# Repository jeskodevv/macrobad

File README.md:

# macropad but its evil >:]

hackclub stardance macropad mission, but its evil. it has shortcuts for things i do frequently, and hyperfocus mode. 

for details about the design process or other information, check out the [stardance devlogs](https://stardance.hackclub.com/projects/25784). A local copy is available in [JOURNAL.md](https://github.com/jeskodevv/macrobad/blob/main/JOURNAL.md).

## WHAT IT HAS

- SEEEDUINO RP2040 MCU
- 5x SWITCHES
- 1X ROTARY KNOB
- 0.91' OLED SCREEN
- RGB LED
- awesome design inspired by original hackpad itself :D

## WHAT IT CAN (FEATURES WIP)

- nothing xD (for now)

## HARDWARE OVERVIEW

**MacroBad :D** is 2-layer Printed Circuit Board and it has **seeeduino rp2040** as its core

here's the schematic

and here's the board design

### BOM

Bill of Materials also available in [BOM.csv](https://github.com/jeskodevv/macrobad/blob/main/BOM.csv) too.

## SOFTWARE OVERVIEW

imagine here's smth meaningful

## LINKS

- [Wiki [WIP]](https://github.com/jeskodevv/motrix/wiki)
- [Development Journal](https://stasis.hackclub.com/dashboard/discover/cmnlk2lji00hk01qlbceh9il3)
- [PCB Gerber Files](https://github.com/jeskodevv/motrix/blob/main/src/PCB/)
- [Arduino Library](https://github.com/jeskodevv/motrix/releases/tag/library)
- [Example Sketches [WIP]](https://github.com/jeskodevv/motrix/tree/main/src/examples)
- [BOM](https://github.com/jeskodevv/motrix/blob/main/BOM.csv)

## LICENSE

the whole project is licensed under **MIT**, meaning you can do whatever with this project.

See [LICENSE](https://github.com/jeskodevv/motrix/blob/main/LICENSE) for full terms.

---

Made with ❤ and [Hack](https://hackclub.com) by [@jeskodevv](https://github.com/jeskodevv)

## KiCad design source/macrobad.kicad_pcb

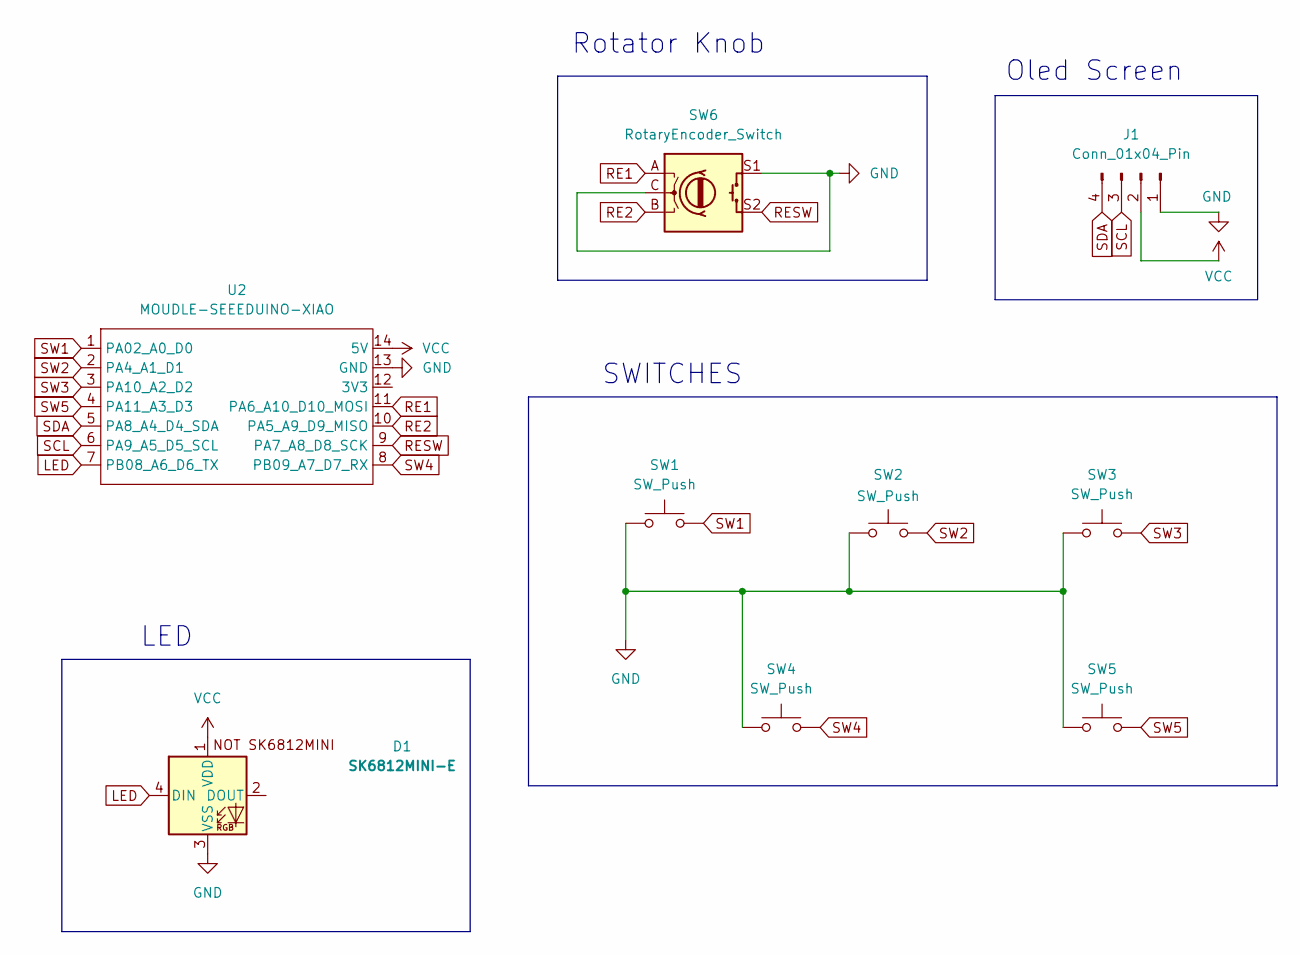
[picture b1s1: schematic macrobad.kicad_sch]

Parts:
D1: SK6812MINI-E; SK6812MINI-E_fixed
J1: Conn_01x04_Pin; SSD1306-0.91-OLED-4pin-128x32
SW1, SW2, SW3, SW5: SW_Push; SW_Cherry_MX_1.00u_PCB
SW4: SW_Push; SW_Cherry_MX_2.00u_PCB
SW6: RotaryEncoder_Switch; RotaryEncoder_Alps_EC11E-Switch_Vertical_H20mm
U2: MOUDLE-SEEEDUINO-XIAO; XIAO-Generic-Hybrid-14P-2.54-21X17.8MM

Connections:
GND: D1.3 (VSS), J1.1, SW1.1, SW2.1, SW3.1, SW4.1, SW5.1, SW6.C, SW6.S1, U2.13 (GND)
LED: D1.4 (DIN), U2.7 (PB08_A6_D6_TX)
RE1: SW6.A, U2.11 (PA6_A10_D10_MOSI)
RE2: SW6.B, U2.10 (PA5_A9_D9_MISO)
RESW: SW6.S2, U2.9 (PA7_A8_D8_SCK)
SCL: J1.3, U2.6 (PA9_A5_D5_SCL)
SDA: J1.4, U2.5 (PA8_A4_D4_SDA)
SW1: SW1.2, U2.1 (PA02_A0_D0)
SW2: SW2.2, U2.2 (PA4_A1_D1)
SW3: SW3.2, U2.3 (PA10_A2_D2)
SW4: SW4.2, U2.8 (PB09_A7_D7_RX)
SW5: SW5.2, U2.4 (PA11_A3_D3)
VCC: D1.1 (VDD), J1.2, U2.14 (5V)

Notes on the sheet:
LED
SWITCHES
Rotator Knob
Oled Screen

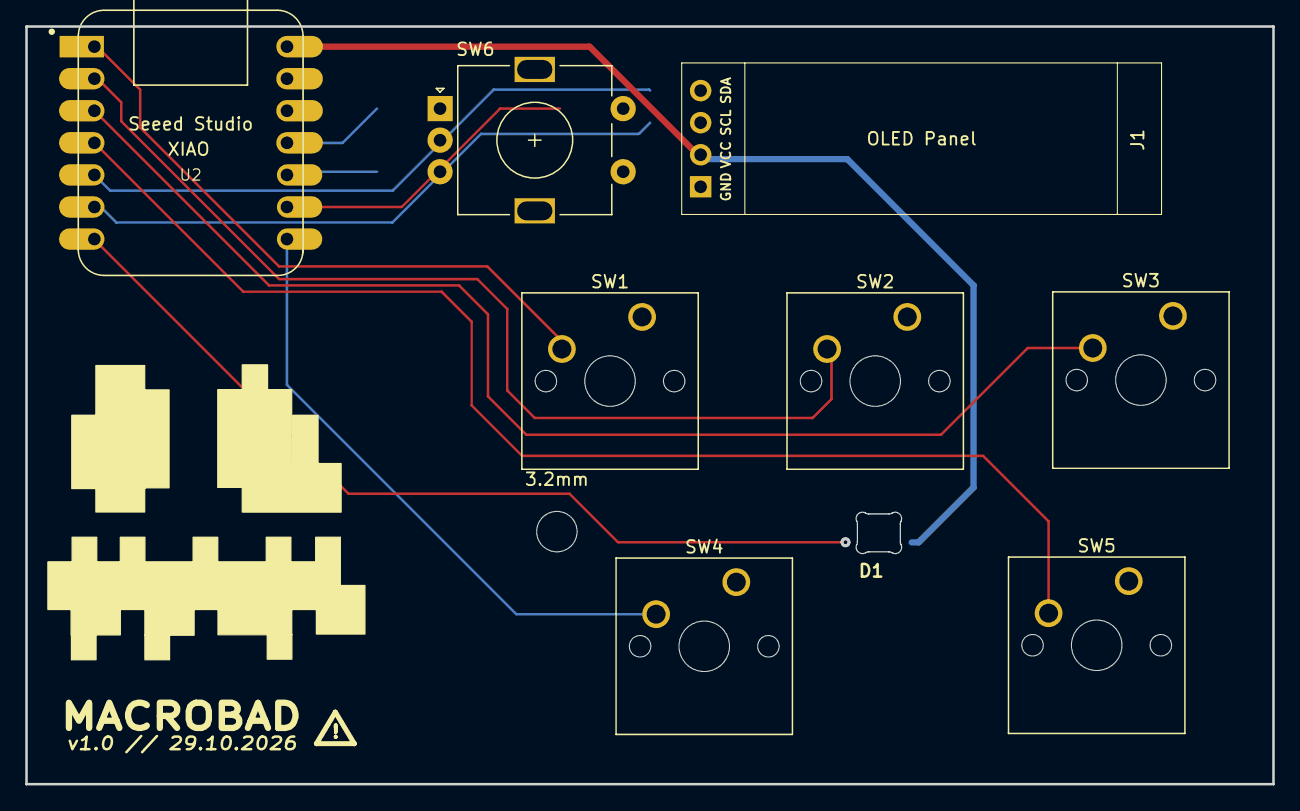
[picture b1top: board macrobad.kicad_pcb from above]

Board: 2 copper layers, 98.8 x 60.0 mm, 10 parts (0 on the bottom side), 13 nets.

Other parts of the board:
3.2mm: MountingHole_3.2mm_M3
